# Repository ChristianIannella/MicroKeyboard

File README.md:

# MicroKeyboard

MicroKeyboard is a small customizable keyboard/mouse.

Based on [ArduinoMicro](https://store.arduino.cc/products/arduino-micro), it allows you to choose the function to be associated with each single key, including encoder and thumbstick.

MicroKeyboard is open-source and open-hardware but you can still decide to buy one already assembled on [Tindie](https://www.tindie.com/products/chris_maker_/microkeyboard/)

<picture><picture>

Thanks to PCBWay for sponsoring this project.

[ITALIANO](https://github.com/ChristianIannella/MicroKeyboard/blob/main/ITALIANO.md)
  
[ENGLISH](https://github.com/ChristianIannella/MicroKeyboard/blob/main/ENGLISH.md)

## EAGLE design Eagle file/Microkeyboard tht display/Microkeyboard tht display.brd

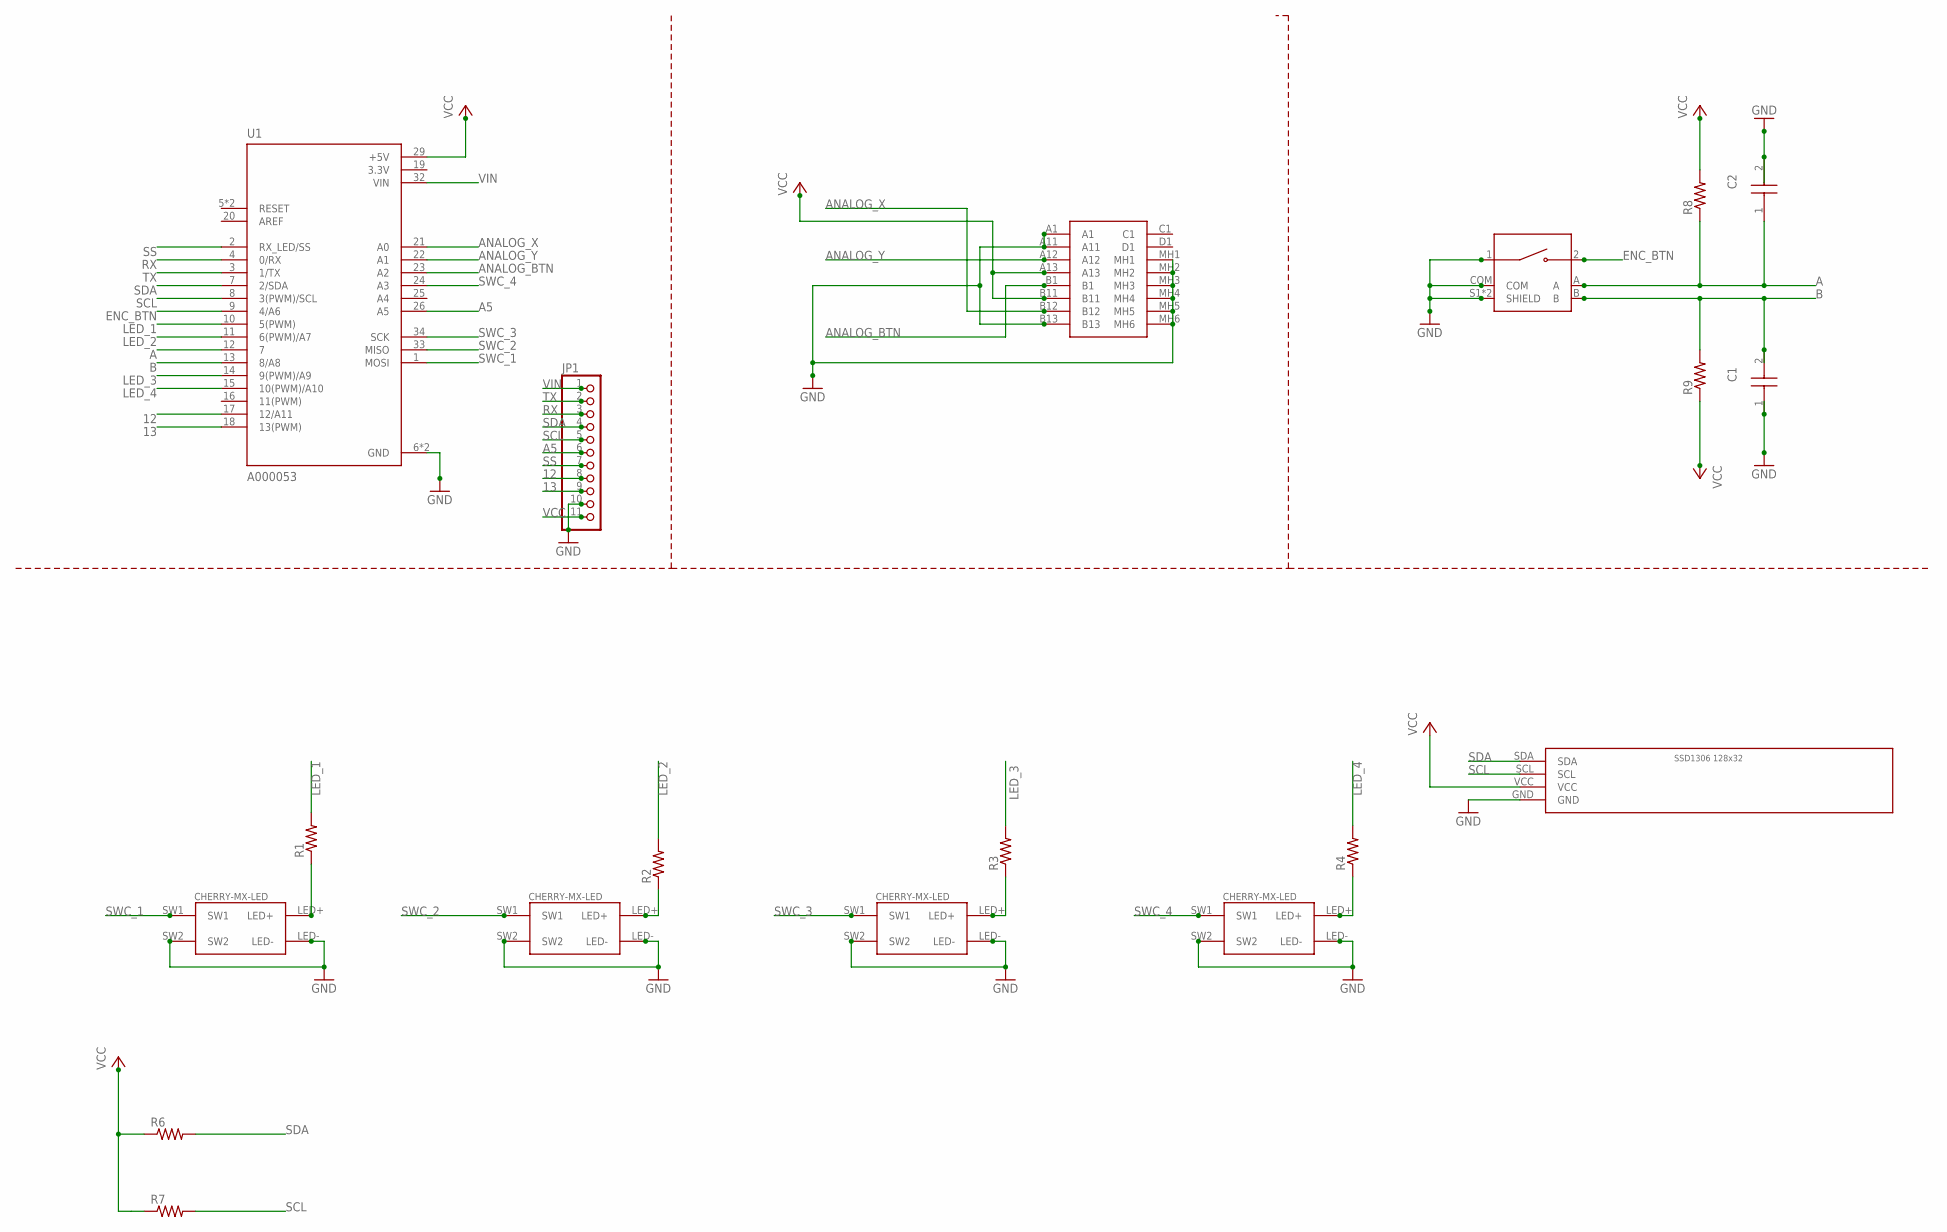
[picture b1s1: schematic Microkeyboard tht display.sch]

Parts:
C1, C2: FG26X7R2E104KNT06; FG26
JP1: PINHD-1X11; 1X11
MT1: PEC11R-4215F-S0024; XDCR_PEC11R-4215F-S0024
R1, R2, R3, R4, R6, R7, R8, R9: R-US_0207/10; 0207/10
S1: RKJXV122400R
SWC_1: SWC_1; CHERRY-MX-LED
U1: A000053; ARDUINO_A000053
U$1, U$2, U$5: CHERRY-MX-LED
U$3: SSD1306_128X32

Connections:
3.3V: U1.19 (3.3V)
12: JP1.8, U1.17 (12/A11)
13: JP1.9, U1.18 (13(PWM))
A: C2.1, MT1.A, R8.1, U1.12 (7)
A5: JP1.6, U1.26 (A5)
ANALOG_BTN: S1.B1, U1.23 (A2)
ANALOG_X: S1.B12, U1.21 (A0)
ANALOG_Y: S1.A12, U1.22 (A1)
B: C1.2, MT1.B, R9.2, U1.13 (8/A8)
ENC_BTN: MT1.2, U1.9 (4/A6)
GND: C1.1, C2.2, JP1.10, MT1.1, MT1.COM, MT1.S1 (SHIELD), MT1.S2 (SHIELD), S1.A1, S1.A11, S1.B13, S1.MH1, S1.MH2, S1.MH3, S1.MH4, S1.MH5, S1.MH6, SWC_1.LED-, SWC_1.SW2, U1.6 (GND), U1.31 (GND), U$1.LED-, U$1.SW2, U$2.LED-, U$2.SW2, U$3.GND, U$5.LED-, U$5.SW2
LED_1: R1.2, U1.10 (5(PWM))
LED_2: R2.2, U1.11 (6(PWM)/A7)
LED_3: R3.2, U1.14 (9(PWM)/A9)
LED_4: R4.2, U1.15 (10(PWM)/A10)
unnamed: R1.1, SWC_1.LED+
unnamed: R3.1, U$1.LED+
unnamed: R2.1, U$5.LED+
unnamed: R4.1, U$2.LED+
RX: JP1.3, U1.4 (0/RX)
SCL: JP1.5, R7.2, U1.8 (3(PWM)/SCL), U$3.SCL
SDA: JP1.4, R6.2, U1.7 (2/SDA), U$3.SDA
SS: JP1.7, U1.2 (RX_LED/SS)
SWC_1: SWC_1.SW1, U1.1 (MOSI)
SWC_2: U1.33 (MISO), U$5.SW1
SWC_3: U1.34 (SCK), U$1.SW1
SWC_4: U1.24 (A3), U$2.SW1
TX: JP1.2, U1.3 (1/TX)
VCC: JP1.11, R6.1, R7.1, R8.2, R9.1, S1.A13, S1.B11, U1.29 (+5V), U$3.VCC
VIN: JP1.1, U1.32 (VIN)

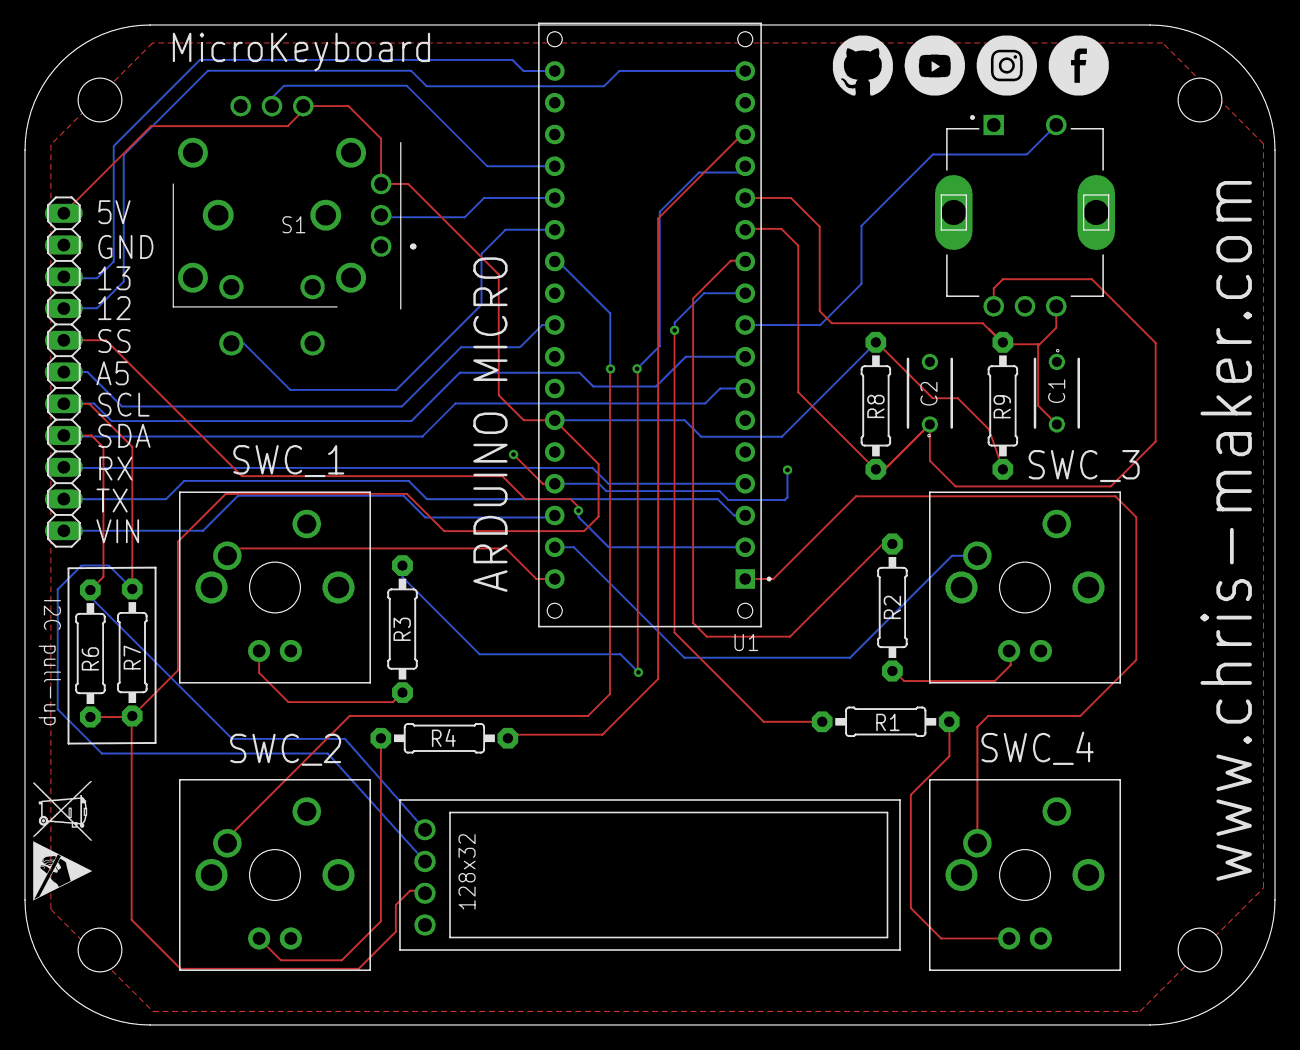
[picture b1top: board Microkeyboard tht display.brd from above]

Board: 2 copper layers, 100.0 x 80.0 mm, 19 parts (0 on the bottom side), 29 nets.

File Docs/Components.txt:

R1 10K
R2 10K
R3 600
R4 600
R5 600
R6 600
R7 600
R8 10K
R9 10K

C1 0.1 uF
C2 0.1 uF

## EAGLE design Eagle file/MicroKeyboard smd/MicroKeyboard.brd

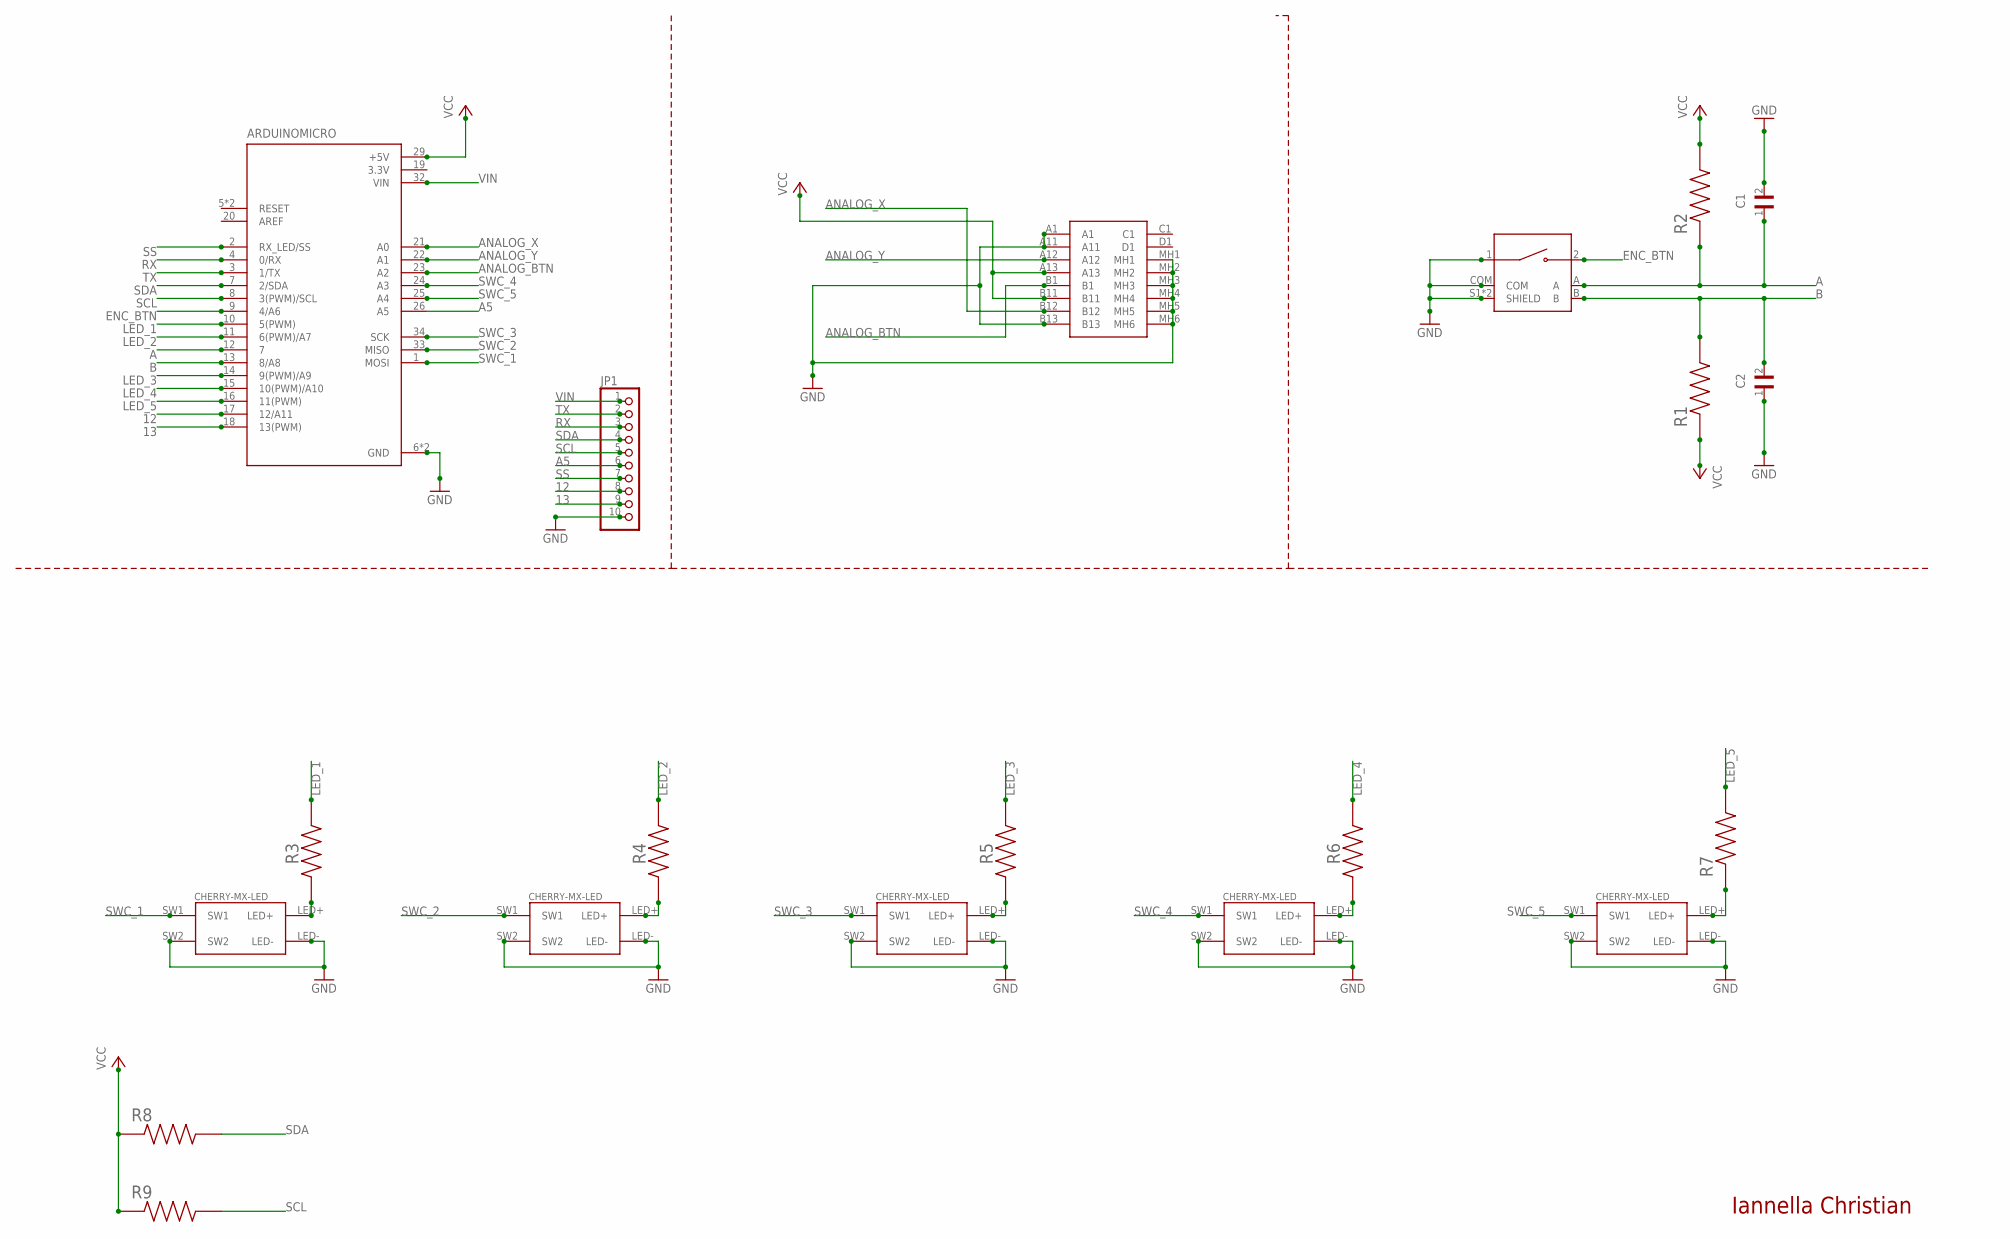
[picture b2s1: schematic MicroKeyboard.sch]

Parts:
ARDUINOMICRO: A000053; ARDUINO_A000053
C1, C2: 0805YC103J4T2A; CAPC2012X94N
JP1: PINHD-1X10; 1X10
MT1: PEC11R-4215F-S0024; XDCR_PEC11R-4215F-S0024
R1, R2, R3, R4, R5, R6, R7, R8, R9: RC0805FR-07330RL; RESC2012X60N
S1: RKJXV122400R
SWC_1: SWC_1; CHERRY-MX-LED
U$1, U$2, U$3, U$5: CHERRY-MX-LED

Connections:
3.3V: ARDUINOMICRO.19 (3.3V)
12: ARDUINOMICRO.17 (12/A11), JP1.8
13: ARDUINOMICRO.18 (13(PWM)), JP1.9
A: ARDUINOMICRO.12 (7), C1.1, MT1.A, R2.1
A5: ARDUINOMICRO.26 (A5), JP1.6
ANALOG_BTN: ARDUINOMICRO.23 (A2), S1.B1
ANALOG_X: ARDUINOMICRO.21 (A0), S1.B12
ANALOG_Y: ARDUINOMICRO.22 (A1), S1.A12
B: ARDUINOMICRO.13 (8/A8), C2.2, MT1.B, R1.2
ENC_BTN: ARDUINOMICRO.9 (4/A6), MT1.2
GND: ARDUINOMICRO.6 (GND), ARDUINOMICRO.31 (GND), C1.2, C2.1, JP1.10, MT1.1, MT1.COM, MT1.S1 (SHIELD), MT1.S2 (SHIELD), S1.A1, S1.A11, S1.B13, S1.MH1, S1.MH2, S1.MH3, S1.MH4, S1.MH5, S1.MH6, SWC_1.LED-, SWC_1.SW2, U$1.LED-, U$1.SW2, U$2.LED-, U$2.SW2, U$3.LED-, U$3.SW2, U$5.LED-, U$5.SW2
LED_1: ARDUINOMICRO.10 (5(PWM)), R3.2
LED_2: ARDUINOMICRO.11 (6(PWM)/A7), R4.2
LED_3: ARDUINOMICRO.14 (9(PWM)/A9), R5.2
LED_4: ARDUINOMICRO.15 (10(PWM)/A10), R6.2
LED_5: ARDUINOMICRO.16 (11(PWM)), R7.2
unnamed: R3.1, SWC_1.LED+
unnamed: R7.1, U$3.LED+
unnamed: R5.1, U$1.LED+
unnamed: R4.1, U$5.LED+
unnamed: R6.1, U$2.LED+
RX: ARDUINOMICRO.4 (0/RX), JP1.3
SCL: ARDUINOMICRO.8 (3(PWM)/SCL), JP1.5, R9.2
SDA: ARDUINOMICRO.7 (2/SDA), JP1.4, R8.2
SS: ARDUINOMICRO.2 (RX_LED/SS), JP1.7
SWC_1: ARDUINOMICRO.1 (MOSI), SWC_1.SW1
SWC_2: ARDUINOMICRO.33 (MISO), U$5.SW1
SWC_3: ARDUINOMICRO.34 (SCK), U$1.SW1
SWC_4: ARDUINOMICRO.24 (A3), U$2.SW1
SWC_5: ARDUINOMICRO.25 (A4), U$3.SW1
TX: ARDUINOMICRO.3 (1/TX), JP1.2
VCC: ARDUINOMICRO.29 (+5V), R1.1, R2.2, R8.1, R9.1, S1.A13, S1.B11
VIN: ARDUINOMICRO.32 (VIN), JP1.1

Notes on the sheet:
Iannella Christian

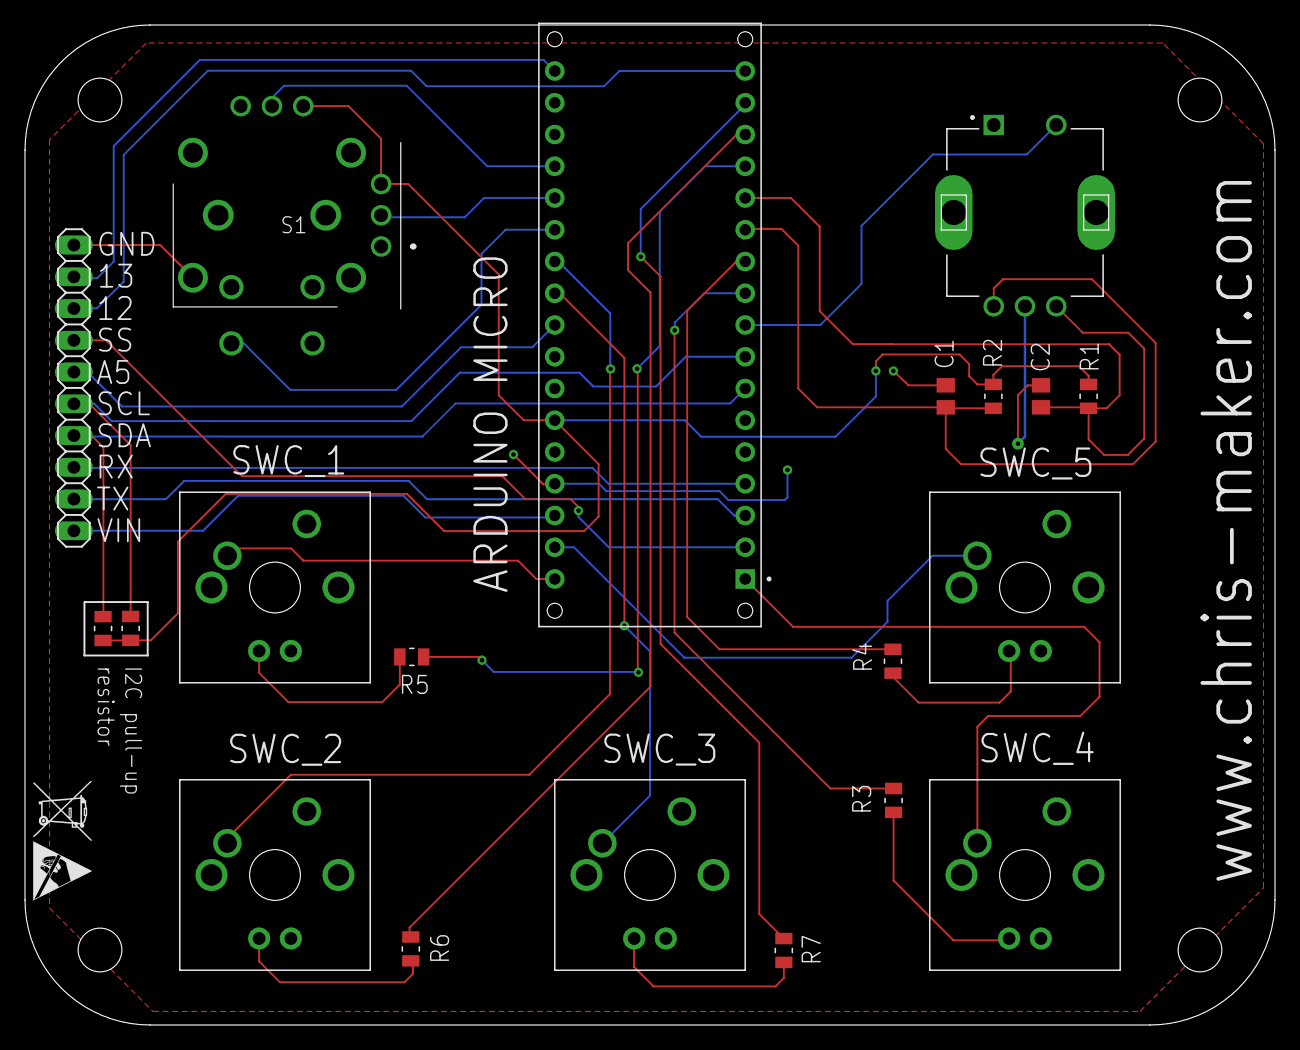
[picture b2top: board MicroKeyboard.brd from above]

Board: 2 copper layers, 100.0 x 80.0 mm, 20 parts (0 on the bottom side), 32 nets.

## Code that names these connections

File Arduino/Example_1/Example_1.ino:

#include <Arduino.h>
#include "HID-Project.h" 
#include <EncoderButton.h>

//#define DEBUG

#define ANALOG_X       18
#define ANALOG_Y       19
#define ANALOG_BTN     20
bool analog_btn_state = false;
int mouse_delay = 20;
bool left_press = false;

#define ENC_A     7
#define ENC_B     8
#define ENC_BTN   4
bool zoom_scroll = false;
EncoderButton eb1(ENC_A, ENC_B, ENC_BTN);

static unsigned long previousMillis2 = 0;
static unsigned long previousMillis = 0; 
const long interval = 3;
int bg_brightness =  10;
int pushed_switch = 0;
bool increase_brightness = true;
bool decrease_brightness = false;

#define SWC_1     15
#define SWC_2     21
#define SWC_3     22
#define SWC_4     16
#define SWC_5     14

#define LED_1     9
#define LED_2     10
#define LED_3     11
#define LED_4     5
#define LED_5     6

bool swc_1_state = false;
bool swc_2_state = false;
bool swc_3_state = false;
bool swc_4_state = false;
bool swc_5_state = false;

void swc_1_pushed(){ // password

  #ifdef DEBUG
    Serial.println("1 pushed");
  #endif

  pushed_switch = LED_1;
  Keyboard.println("your_password");
}

void swc_2_pushed(){ // email address

  #ifdef DEBUG
    Serial.println("2 pushed");
  #endif

  pushed_switch = LED_2;
  Keyboard.print("your_mail");
}

void swc_3_pushed(){ // clic cancel

  #ifdef DEBUG
    Serial.println("3 pushed");
  #endif

  pushed_switch = LED_3;
  BootKeyboard.write(KEY_DELETE);
}

void swc_4_pushed(){ // clic mouse left button

  #ifdef DEBUG
    Serial.println("4 pushed");
  #endif

  pushed_switch = LED_4;
  AbsoluteMouse.click(MOUSE_LEFT);
}

void swc_5_pushed(){ // press/release mouse left button

  #ifdef DEBUG
    Serial.println("5 pushed");
  #endif

  pushed_switch = LED_5;

  if (left_press == false) {
    AbsoluteMouse.press(MOUSE_LEFT);
    digitalWrite(LED_BUILTIN, HIGH);
    left_press = true;
  }
  else if(left_press == true){
    AbsoluteMouse.release(MOUSE_LEFT);
    digitalWrite(LED_BUILTIN, LOW);
    left_press = false;
  }
}

void analog_btn_pushed(){

  #ifdef DEBUG
    Serial.println("Analog pushed");
  #endif

  AbsoluteMouse.click(MOUSE_RIGHT);

}

void onEb1Clicked(EncoderButton& eb) {

  #ifdef DEBUG
    Serial.println("Encoder pushed");
  #endif

  if (eb.clickCount()== 1){
    zoom_scroll = !zoom_scroll;
    
  }
  else if (eb.clickCount()== 2){
    //pass 
  }
}

void onEb1Encoder(EncoderButton& eb) {

  if (eb.increment() == 1){

    #ifdef DEBUG
      Serial.println("Encoder +");
    #endif

    if (zoom_scroll == false){
      Mouse.move(0,0,1); 
    }
    else{
      Keyboard.press(KEYPAD_ADD); 
      delay(50);
      Keyboard.releaseAll(); 
    }
  }
  else if (eb.increment() == -1){

    #ifdef DEBUG
      Serial.println("Encoder -");
    #endif

    if (zoom_scroll == false){
      Mouse.move(0,0,-1); 
    }
    else {
      Keyboard.press(KEYPAD_SUBTRACT); 
      delay(50);
      Keyboard.releaseAll(); 
    }
  }
  //eb.position();
}

void check_button_press(){

  if (swc_1_state == false){
    if (digitalRead(SWC_1)==LOW){
      delay(20);
      if (digitalRead(SWC_1)==LOW){
        swc_1_state = true;
        swc_1_pushed(); 
      }
    }    
  }
  if (digitalRead(SWC_1)==HIGH){
    swc_1_state = false;
  }

    if (swc_2_state == false){
    if (digitalRead(SWC_2)==LOW){
      delay(20);
      if (digitalRead(SWC_2)==LOW){
        swc_2_state = true;
        swc_2_pushed(); 
      }
    }    
  }
  if (digitalRead(SWC_2)==HIGH){
    swc_2_state = false;
  }

  if (swc_3_state == false){
    if (digitalRead(SWC_3)==LOW){
      delay(20);
      if (digitalRead(SWC_3)==LOW){
        swc_3_state = true;
        swc_3_pushed(); 
      }
    }    
  }
  if (digitalRead(SWC_3)==HIGH){
    swc_3_state = false;
  }

  if (swc_4_state == false){
    if (digitalRead(SWC_4)==LOW){
      delay(20);
      if (digitalRead(SWC_4)==LOW){
        swc_4_state = true;
        swc_4_pushed(); 
      }
    }    
  }
  if (digitalRead(SWC_4)==HIGH){
    swc_4_state = false;
  }

  if (swc_5_state == false){
    if (digitalRead(SWC_5)==LOW){
      delay(20);
      if (digitalRead(SWC_5)==LOW){
        swc_5_state = true;
        swc_5_pushed(); 
      }
    }    
  }
  if (digitalRead(SWC_5)==HIGH){
    swc_5_state = false;
  }

  if (analog_btn_state == false){
    if (digitalRead(ANALOG_BTN)==LOW){
      delay(20);
      if (digitalRead(ANALOG_BTN)==LOW){
        analog_btn_state = true;
        analog_btn_pushed(); 
      }
    }    
  }
  if (digitalRead(ANALOG_BTN)==HIGH){
    analog_btn_state = false;
  }

}

void led_effect(){

  if (pushed_switch != 0) {

    if (increase_brightness == true){

      if(bg_brightness <= 240) {
        bg_brightness += 10;
        analogWrite(pushed_switch, bg_brightness);
      }
      else if(bg_brightness > 240){
        increase_brightness = false;
        decrease_brightness = true;
      }
    }
    if(decrease_brightness == true) {
      if(bg_brightness > 10) {
        bg_brightness -= 10;
        analogWrite(pushed_switch, bg_brightness);
      }
      else if(bg_brightness == 10){
        increase_brightness = true;
        decrease_brightness = false;
        pushed_switch = 0;
      }
    }
  }
}

void mouse_move(int x, int y){

  int delta_x = 0;
  int delta_y = 0;

  if (x>600){
    int i = map(x,600,1024,1,15);
    delta_x=i; 
  } 

  else if (x<400){
    int i = map(x,400,0,1,15);
    delta_x=-i; 
  } 
  
  if (y>600) {
    int l = map(y,600,1024,1,15);
    delta_y=-l; 
  } 

  else if (y<400){
    int l = map(y,400,0,1,15);
    delta_y=l;  
  } 
  
  Mouse.move(delta_x,delta_y,0); 

  }

void setup() {

  #ifdef DEBUG
    Serial.begin(9600);
  #endif

  pinMode(LED_BUILTIN, OUTPUT);

  pinMode(SWC_1, INPUT_PULLUP);
  pinMode(SWC_2, INPUT_PULLUP);
  pinMode(SWC_3, INPUT_PULLUP);
  pinMode(SWC_4, INPUT_PULLUP);
  pinMode(SWC_5, INPUT_PULLUP);

  pinMode(ANALOG_BTN, INPUT_PULLUP);

  pinMode(LED_1, OUTPUT);
  pinMode(LED_2, OUTPUT);
  pinMode(LED_3, OUTPUT);
  pinMode(LED_4, OUTPUT);
  pinMode(LED_5, OUTPUT);
  
  for (int i = 0; i <= 250; i+=10) {
    analogWrite(LED_1,i);
    analogWrite(LED_2,i);
    analogWrite(LED_3,i);
    analogWrite(LED_4,i);
    analogWrite(LED_5,i);
    delay(7);
  }
  for (int i = 250; i >= bg_brightness; i-=10) {
    analogWrite(LED_1,i);
    analogWrite(LED_2,i);
    analogWrite(LED_3,i);
    analogWrite(LED_4,i);
    analogWrite(LED_5,i);
    delay(7);
  }
  
  Keyboard.begin();
  Mouse.begin();

  eb1.setClickHandler(onEb1Clicked);
  eb1.setEncoderHandler(onEb1Encoder);

}

void loop() {

  unsigned long currentMillis = millis();

  eb1.update();

  check_button_press();

  if (currentMillis - previousMillis >= interval) {
    previousMillis = currentMillis;
    led_effect();
  } 

   int x = analogRead(ANALOG_X);
   int y = analogRead(ANALOG_Y);
   
   if (previousMillis2 > millis()) previousMillis2 = millis(); 

   if (millis() - previousMillis2 > mouse_delay) 
    {
    mouse_move(x,y);
    previousMillis2 = millis();
    }
} 

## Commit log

2023-07-18 Upload docs
2023-07-18 v1.0
2023-09-28 Update LICENSE
